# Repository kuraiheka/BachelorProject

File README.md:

Code for our bachelor project. Not intended for public consumption.

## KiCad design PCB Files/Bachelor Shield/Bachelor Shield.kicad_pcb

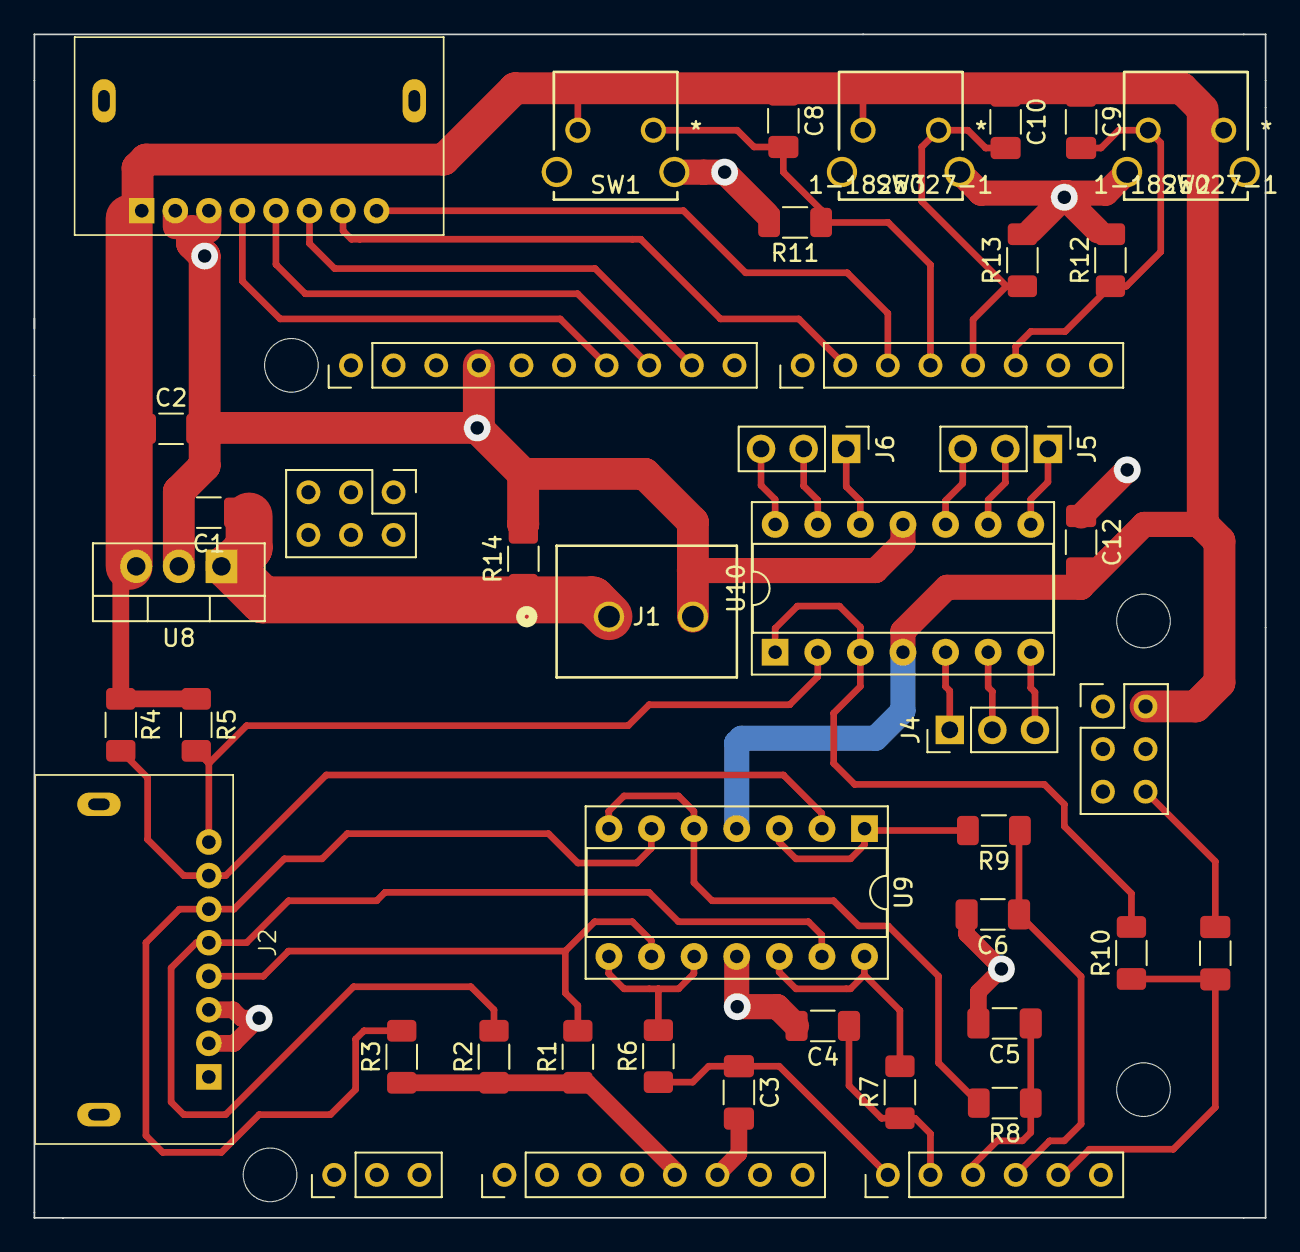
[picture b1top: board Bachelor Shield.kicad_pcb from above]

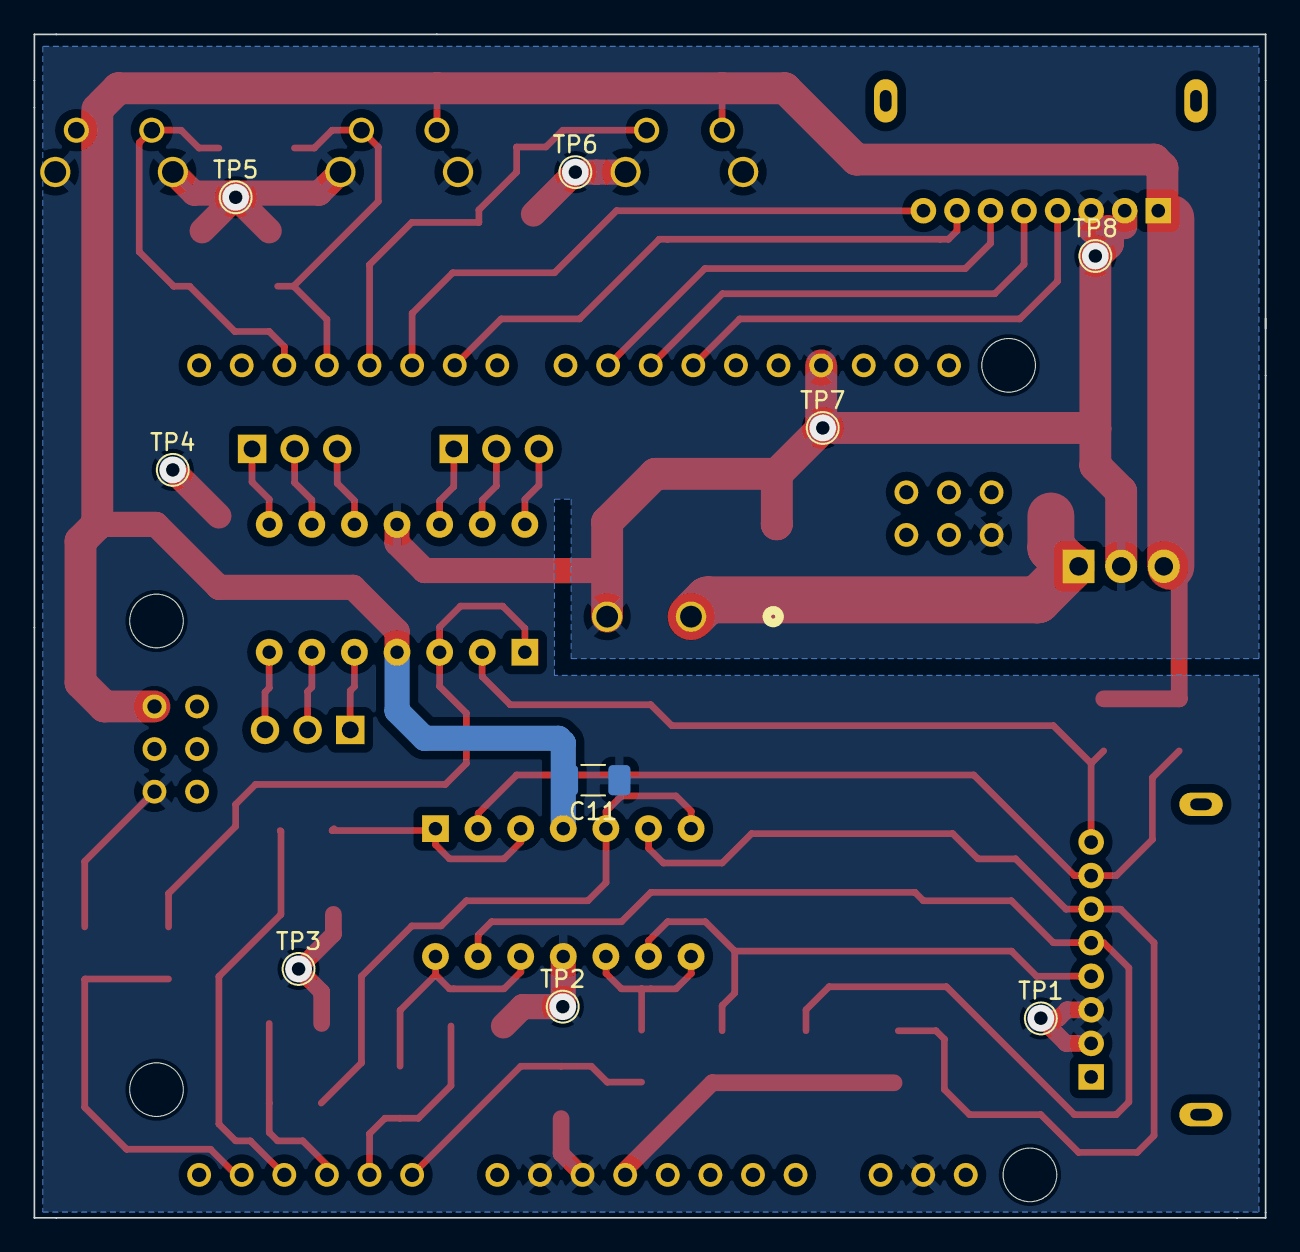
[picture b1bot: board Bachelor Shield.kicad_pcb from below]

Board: 2 copper layers, 73.4 x 70.6 mm, 57 parts (9 on the bottom side), 35 nets.

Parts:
C1, C2, C3, C4, C5, C6, C7, C8, C9, C10, C11, C12: C; C_1206_3216Metric_Pad1.33x1.80mm_HandSolder
H1: MountingHole1; Arduino_MountingHole
H2: MountingHole2; Arduino_MountingHole
H3: MountingHole3; Arduino_MountingHole
H4: MountingHole4; Arduino_MountingHole
J1: Power Input; CONN_TB002-500-02BE_CUD
J2: Flex Input; Molex_2200301081
J3: Motor Output; Molex_2200301081
J4, J5, J6: Spare Opamp; PinHeader_1x03_P2.54mm_Vertical
R1, R2, R3, R4, R5, R6, R7, R8, R9, R10, R11, R12, R13, R14: R; R_1206_3216Metric_Pad1.30x1.75mm_HandSolder
SW1, SW2, SW3: 1-1825027-1
TP1, TP2, TP3, TP4, TP5, TP6, TP7, TP8: TestPoint; TestPoint_Pad_D1.5mm
U1: OFF; Arduino_PinSocket_1x03_P2.54mm_Vertical
U2: Analog_1; Arduino_PinSocket_1x08_P2.54mm_Vertical
U3: Analog_2; Arduino_PinSocket_1x06_P2.54mm_Vertical
U4: ESP32-S3; Arduino_PinSocket_2x03_P2.54mm_Vertical
U5: ICSP; Arduino_PinSocket_2x03_P2.54mm_Vertical
U6: Digital_1; Arduino_PinSocket_1x10_P2.54mm_Vertical
U7: Digital_2; Arduino_PinSocket_1x08_P2.54mm_Vertical
U8: L7805; TO-220-3_Vertical
U9, U10: Opamp_Quad; DIP-14_W7.62mm_Socket

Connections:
+5V: C2.1, C8.1, C9.1, C10.1, C11.2, C12.2, J3.1, R1.1, R2.1, R3.1, R4.1, R5.1, SW1.2, SW2.1, SW3.2, U2.5 (+5V), U5.2 (+5V), U8.3 (OUT), U9.4 (V+), U10.4 (V+)
+BATT: C1.1, J1.1, R14.1, U8.1 (IN)
Down Button: C9.2, R12.1, SW2.2, U7.16 (D2)
Flex Signal 1: C3.1, R6.1, U3.9 (A0)
Flex Signal 2: C4.1, R7.1, U3.10 (A1)
Flex Signal 3: C5.1, R8.1, U3.11 (A2)
Flex Signal 4: C6.1, R9.1, U3.12 (A3)
Flex Signal 5: C7.1, R10.1, U3.13 (A4)
GND: C1.2, C2.2, C3.2, C4.2, C5.2, C6.2, C7.2, C11.1, C12.1, J1.2, J2.2, J2.3, J3.2, J3.3, R11.2, R12.2, R13.2, R14.2, SW1.3, SW1.4, SW2.3, SW2.4, SW3.3, SW3.4, TP1.1, TP2.1, TP3.1, TP4.1, TP5.1, TP6.1, TP7.1, TP8.1, U1.2 (GND), U2.6 (GND), U2.7 (GND), U4.6 (GND), U5.6 (GND), U6.4 (GND), U8.2 (GND), U9.11 (V-), U10.11 (V-)
Motor Signal 1: J3.4, U6.7 (~D11/COPI)
Motor Signal 2: J3.5, U6.8 (~D10/CS/CANTX0)
Motor Signal 3: J3.6, U6.9 (~D9)
Motor Signal 4: J3.7, U7.12 (~D6)
Motor Signal 5: J3.8, U7.13 (~D5)
unnamed: J2.4, R1.2, U9.9 (-)
unnamed: J2.5, R2.2, U9.13 (-)
unnamed: J2.6, R3.2, U9.6 (-)
unnamed: J2.7, R4.2, U9.2 (-)
unnamed: J2.8, R5.2, U10.2 (-)
unnamed: J4.1, U10.5 (+)
unnamed: J4.2, U10.6 (-)
unnamed: J4.3, U10.7
unnamed: J5.1, U10.8
unnamed: J5.2, U10.9 (-)
unnamed: J5.3, U10.10 (+)
unnamed: J6.1, U10.12 (+)
unnamed: J6.2, U10.13 (-)
unnamed: J6.3, U10.14
unnamed: R9.2, U9.1, U9.3 (+)
unnamed: R8.2, U9.5 (+), U9.7
unnamed: R6.2, U9.8, U9.10 (+)
unnamed: R7.2, U9.12 (+), U9.14
unnamed: R10.2, U10.1, U10.3 (+)
Shift Button: C10.2, R13.1, SW3.1, U7.15 (~D3)
Up Button: C8.2, R11.1, SW1.1, U7.14 (D4)

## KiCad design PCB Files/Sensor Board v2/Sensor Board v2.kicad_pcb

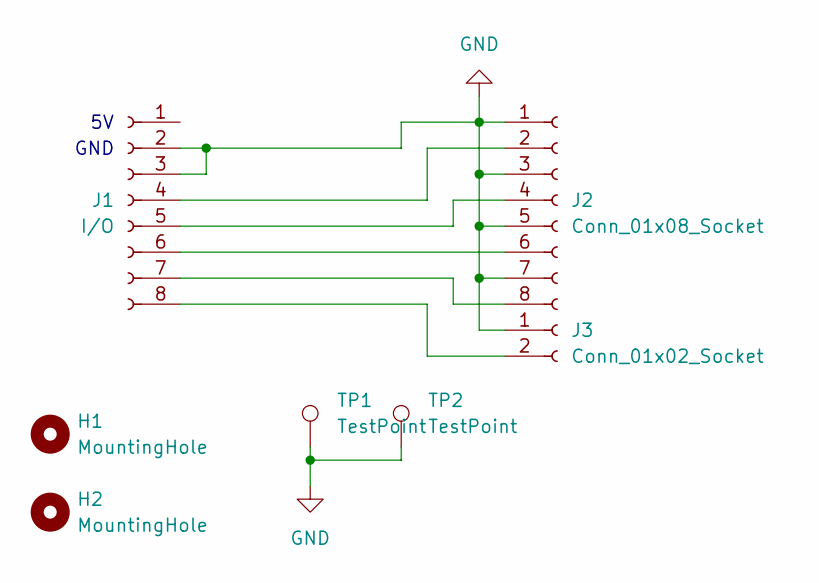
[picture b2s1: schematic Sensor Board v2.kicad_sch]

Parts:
H1, H2: MountingHole; MountingHole_2.2mm_M2
J1: I/O; Molex_2200301081
J2: Conn_01x08_Socket; CUI_TB006-508-08BE
J3: Conn_01x02_Socket; CONN_TB006-508-02_CUD
TP1, TP2: TestPoint; TestPoint_Pad_D1.5mm

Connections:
GND: J1.2, J1.3, J2.1, J2.3, J2.5, J2.7, J3.1, TP1.1, TP2.1
unnamed: J1.4, J2.2
unnamed: J1.5, J2.4
unnamed: J1.6, J2.6
unnamed: J1.7, J2.8
unnamed: J1.8, J3.2

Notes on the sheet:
GND

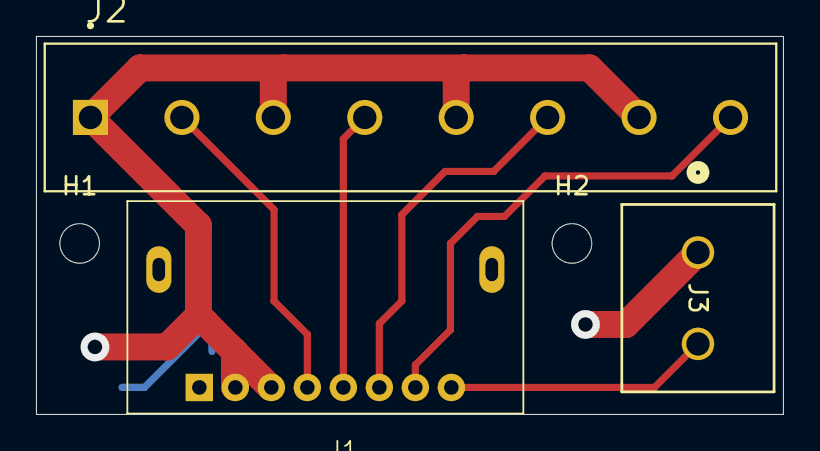
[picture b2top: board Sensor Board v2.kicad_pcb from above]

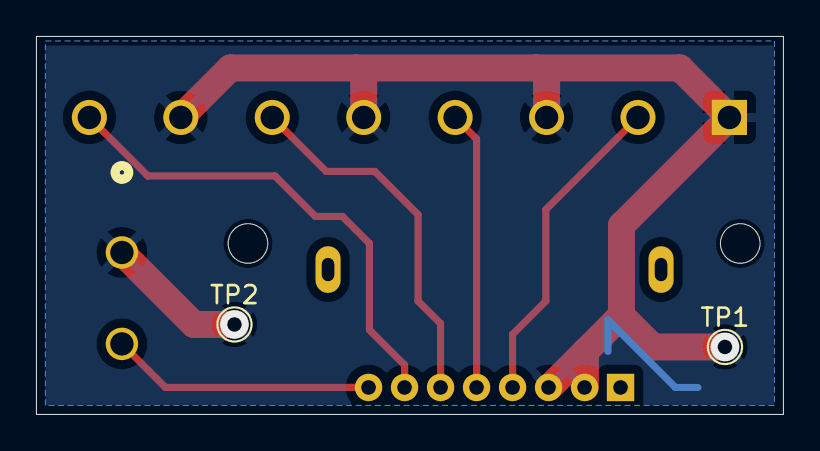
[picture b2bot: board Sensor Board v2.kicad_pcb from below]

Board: 2 copper layers, 41.5 x 21.0 mm, 7 parts (2 on the bottom side), 6 nets.

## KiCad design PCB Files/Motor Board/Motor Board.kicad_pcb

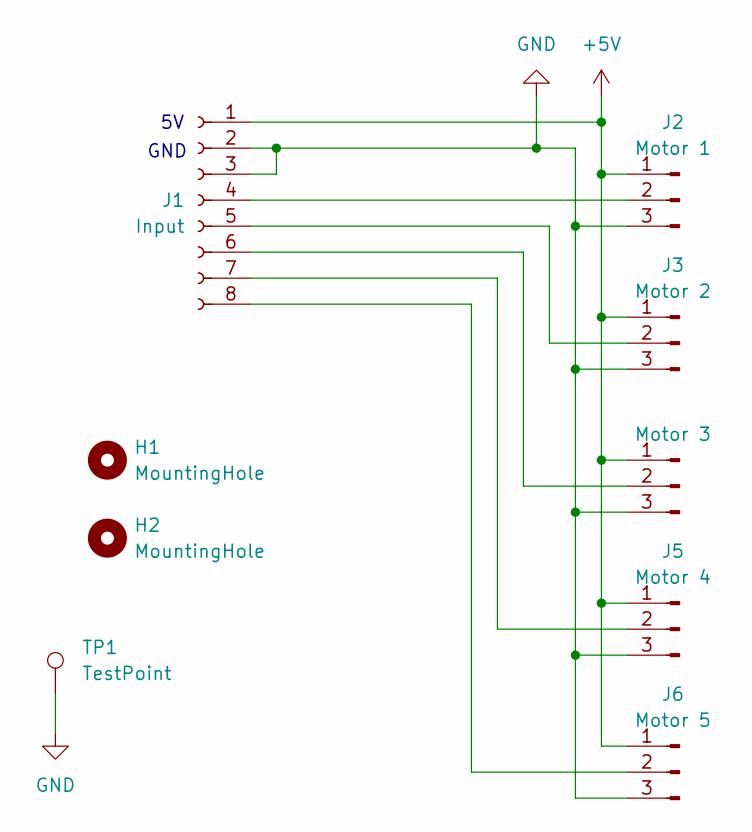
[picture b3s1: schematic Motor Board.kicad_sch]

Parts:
H1, H2: MountingHole; MountingHole_2.2mm_M2
J1: Input; Molex_2200291085
J2: Motor 1; PinHeader_1x03_P2.54mm_Horizontal
J3: Motor 2; PinHeader_1x03_P2.54mm_Horizontal
J4: Motor 3; PinHeader_1x03_P2.54mm_Horizontal
J5: Motor 4; PinHeader_1x03_P2.54mm_Horizontal
J6: Motor 5; PinHeader_1x03_P2.54mm_Horizontal
TP1: TestPoint; TestPoint_Pad_D1.5mm

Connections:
+5V: J1.1, J2.1, J3.1, J4.1, J5.1, J6.1
GND: J1.2, J1.3, J2.3, J3.3, J4.3, J5.3, J6.3, TP1.1
unnamed: J1.4, J2.2
unnamed: J1.5, J3.2
unnamed: J1.6, J4.2
unnamed: J1.7, J5.2
unnamed: J1.8, J6.2

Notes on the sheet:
GND

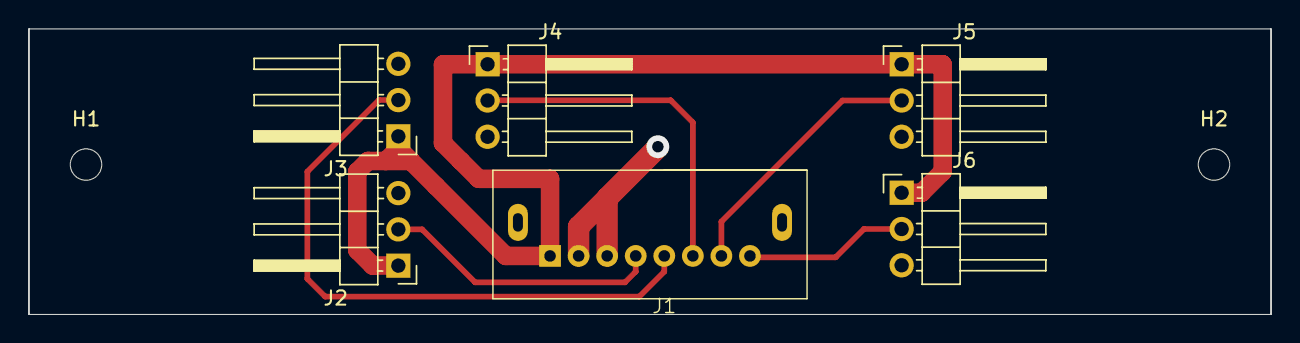
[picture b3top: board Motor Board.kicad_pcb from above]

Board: 2 copper layers, 87.0 x 20.0 mm, 9 parts (1 on the bottom side), 7 nets.

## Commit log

2024-02-23 Add files via upload
    Ikke ferdig
2024-04-22 Revert "Add files via upload"
    This reverts commit ca217c87d8a2c0d947ec75824c5118caad07457c.
2024-04-22 Revert "Add files via upload"
    This reverts commit 9594d40337bb1fdb55546b9e96cd5e65a36dec1a.
2024-04-24 Added servo adjustment functionality
2024-05-26 Everything included

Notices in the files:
parts and their libraries:
Copyright 2016 Accelerated Designs. All rights reserved.
